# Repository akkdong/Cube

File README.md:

# M1
ESP32_WT32-SC01, Barometer, GPS, Audio, Battery bank

# M2
ESP32-S3-HMI-V3, Barometer, GPS, Audio, SD, Battery charge

# M3
M5Paper, EPS32-C3, Baromter, GPS, Audio

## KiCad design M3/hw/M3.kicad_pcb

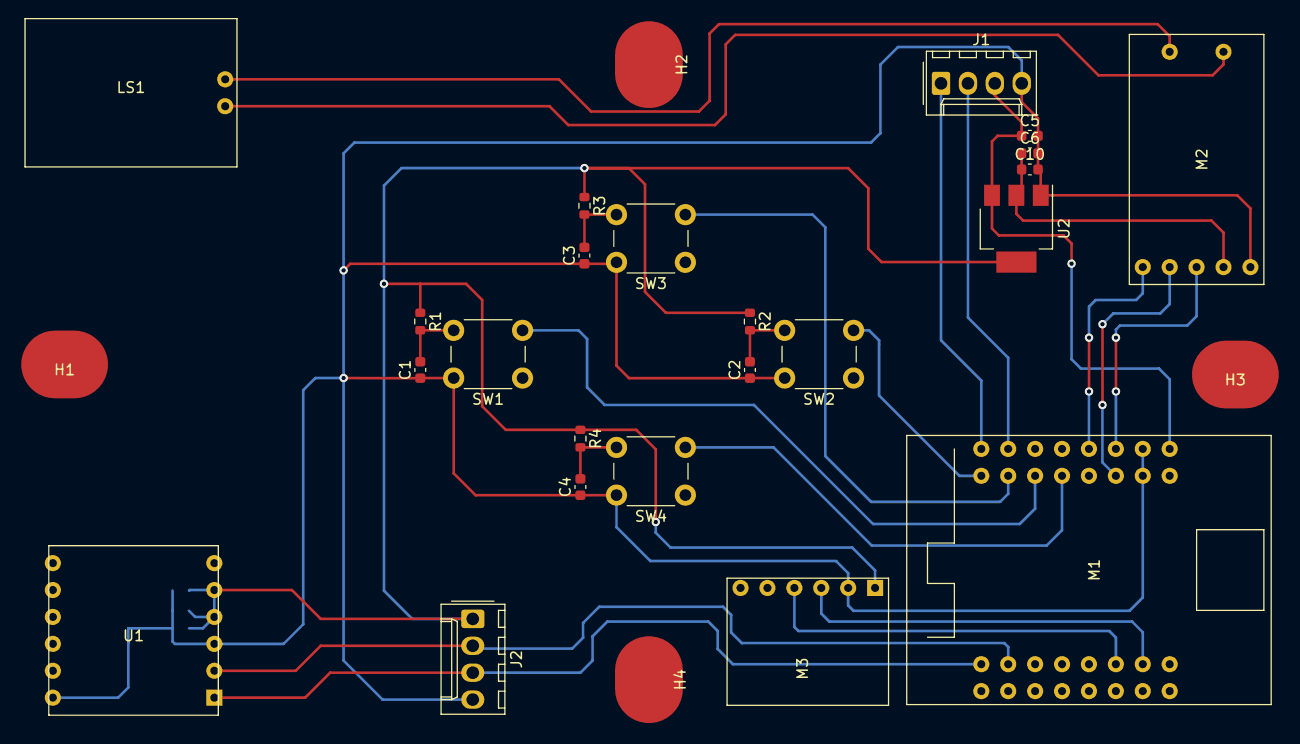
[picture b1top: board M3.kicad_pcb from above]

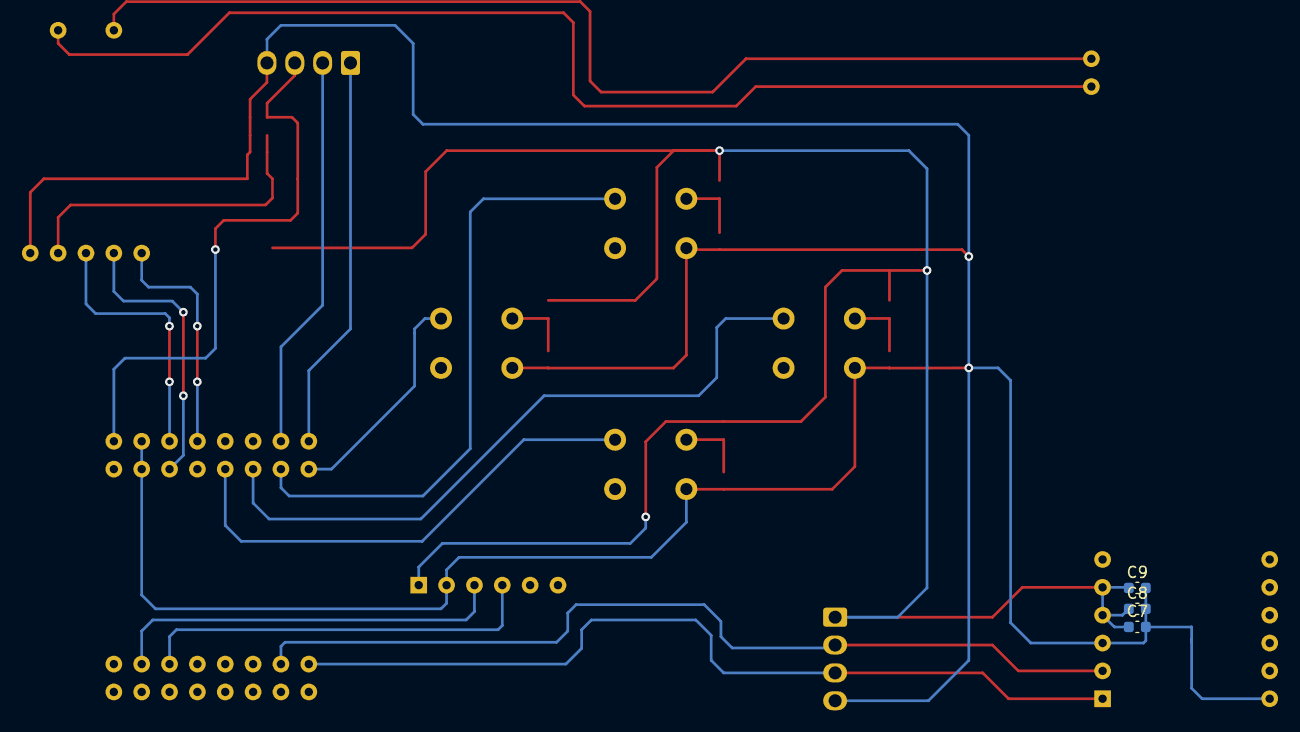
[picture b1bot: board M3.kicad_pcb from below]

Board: 2 copper layers, 30 parts (3 on the bottom side), 18 nets.

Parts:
C1, C2, C3, C4, C8, C9, C10: 0.1uF; C_0603_1608Metric
C5, C6, C7: 10uF; C_0603_1608Metric
H1, H2, H3, H4: MountingHole; M3_HOLE
J1, J2: Conn_01x04; Molex_KK-254_AE-6410-04A_1x04_P2.54mm_Vertical
LS1: Speaker; ROUND-SPEKAER
M1: EPS32S2-MINI; ESP32S2-MINI
M2: PAM8302A
M3: GY-BMP280
R1, R2, R3, R4: 10K; R_0603_1608Metric
SW1, SW2, SW3, SW4: SW_DIP_x01; SW_PUSH_6mm
U1: L80
U2: AP1117-33; SOT-223-3_TabPin2

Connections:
AUDIO+: M1.26, M2.1
AUDIO-: M1.27, M2.2
BARO_SCL: M1.14, M3.3
BARO_SDA: M1.12, M3.4
GND: C1.1, C2.1, C3.1, C4.1, C5.2, C6.2, C7.2, C8.2, C9.2, C10.2, J1.4, J2.4, M1.29, M1.30, M2.5, M3.2, SW1.1, SW2.1, SW3.1, SW4.1, U1.3, U1.12, U2.1
GPS_RX: J2.3, M1.2, U1.1
GPS_TX: J2.2, M1.4, U1.2
HOST_RX: J1.2, M1.20
HOST_TX: J1.1, M1.18
KEY_DOWN: C4.2, M1.23, R4.2, SW4.2
KEY_LEFT: C1.2, M1.21, R1.2, SW1.2
KEY_RIGHT: C2.2, M1.17, R2.2, SW2.2
KEY_UP: C3.2, M1.19, R3.2, SW3.2
MUTE: M1.28, M2.3
unnamed: LS1.1, M2.6
unnamed: LS1.2, M2.7
VBUS: C5.1, J1.3, M1.32, U2.3
VCC: C6.1, C7.1, C8.1, C9.1, C10.1, J2.1, M2.4, M3.1, R1.1, R2.1, R3.1, R4.1, U1.4, U1.5, U2.2

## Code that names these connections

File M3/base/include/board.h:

// board.h
//

#ifndef __BOARD_H__
#define __BOARD_H__

#define GPIO_I2C_SDA        (10)
#define GPIO_I2C_SCL        (13)

#define UART_HOST_RX        (39)    // device-side rx (host-side tx)
#define UART_HOST_TX        (37)    // device-side tx (host-side rx)

#define UART_GPS_RX         (2)     // device-side rx (gps-side tx)
#define UART_GPS_TX         (1)     // device-side tx (gps-side rx)

#define GPIO_KEY_UP         (38)
#define GPIO_KEY_DOWN       (34)
#define GPIO_KEY_LEFT       (36)
#define GPIO_KEY_RIGHT      (40)


#endif // __BOARD_H__

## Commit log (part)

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2022-09-07 documents
2022-09-07 images
2022-09-07 basic
2022-09-08 simulator
2022-09-08 logger
2022-09-12 page, box
2022-09-12 layout (TBD)
2022-09-15 filters
2022-09-15 esp32 port implement (not tested)
2022-09-15 bme280: disable humidity features & optimize
2022-09-15 refactoring
2022-09-15 fixed running-error
2022-09-16 tone play
2022-09-19 case-design
2022-09-19 update case-design
2022-09-19 readme
2022-09-20 update filter
2022-09-24 fixed build-error
2022-09-25 esp32 bt
2022-09-27 BLEVario reference
2022-09-27 acoustic test
2022-09-27 fixed ble-uart write error
2022-10-03 fixed build error
2022-10-03 update working-image
2022-10-03 implement annunciator (TBD)
2022-10-05 filter(kf4d) calibration
2022-10-16 timezone API & fixed filter error
2022-10-18 datasheet
2022-10-19 M2 H/W Test (TBD)
2022-10-19 H/W Test: touch
2022-10-20 H/W Test : lcd w/ lvgl (need test)
2022-10-20 H/W Test: audio, adc (TBD)
2022-10-23 M2 Test code
2022-10-23 M2 case
2022-10-23 HW Test : audio
2022-10-30 fixed layout
2022-10-30 calibrate kalman-filter
2022-10-31 update M2 variometer
2022-11-02 audio-test
2022-11-04 apply vario sound
2022-11-07 test keypad
2022-11-09 widget (working)
2022-11-13 new ui-framework
2022-11-13 startup window & variometer widget
2022-11-14 layout switching
2022-11-15 widgets
2022-11-15 setting-window skeleton
2022-11-16 setting skeleton
2022-11-16 use millis() instead get_tick()
2022-11-17 startup
2022-11-18 compass
2022-11-26 thermal-assistant
2022-11-28 use task
2022-11-30 task
2022-11-30 annunciator
2022-12-01 alert
2022-12-01 M2 new-ui
2022-12-03 new assets
2022-12-05 fixed simulator keypad-handler
2022-12-06 assets
2022-12-07 fixed igc-logging error
2022-12-07 32-icon
2022-12-07 missing files
2022-12-10 fixed nmea loosing
2022-12-10 move Accumulator
2022-12-14 test code
2022-12-21 M1 test...
2022-12-22 m2 refactoring (TBD)
2022-12-23 m2 refactoring(TBD)
2022-12-26 m2 refactoring
2022-12-27 pre-read
2022-12-28 tune
2023-01-07 refactory variometer bar
2023-03-08 rename
2023-03-09 m3 base & disp firmware
2023-03-12 add missing files
2023-03-12 beep
2023-03-13 m3 case
2023-04-03 fixed error of uart initialize
2023-04-13 cube nmea-sentence
2023-04-17 nmea parser (TBD)
2023-04-17 host command
2023-04-19 nmea parsing (TBD)
2023-04-20 show nmea data
2023-04-21 fixed nmea parsing
2023-08-02 M3 test code
2023-08-02 test
2023-08-03 M3 working (compile only)
2023-08-04 running test
2023-08-06 fixed SD error
2023-08-07 thermal assist (TBD)
2023-08-07 change icon-images
2023-08-08 changed source tree
2023-08-09 igc logger
2023-08-11 message box
2023-08-11 suppress log
2023-08-12 page
2023-08-12 changed baro-filter
2023-08-12 barometer
2023-08-12 m3 working
2023-08-16 fixed error of data loosing (TBD)
2023-08-18 pin task to core
2023-08-21 share SPI
2023-08-22 data
2023-08-22 remove unused sources
2023-08-22 pre-shutdown (?)
2023-08-24 fixed vario-logger error
2023-08-24 v-box types
2023-08-24 revert compile option
2023-09-01 top-menu
2023-09-16 change tone-table
2023-09-17 WiFiSetting (TBD)
2023-09-20 captive-portal (TBD)
2023-09-20 use full file-name
2023-09-21 web-service test server
2023-09-21 captive-portal:async (TBD)
2023-09-22 rollback to WebServer
2023-09-22 WebServer build configuration
2023-09-24 async-web-server again
2023-09-24 json type error, web pages, chunked file, bt end
2023-09-28 draw wifi setting page
2023-10-07 fixed label
2023-10-12 load xctask
2023-10-12 xctask sample
2023-10-14 task-simulator: load task & find optimized path
2023-10-14 recompute from pilot position
2023-10-14 xctrack is inherited from xcroute
2023-10-14 race-simulator image
2023-10-15 utils_geographiclib
2023-10-15 xctask test on target
2023-10-18 - changed geographiclib precision - some test code - and so on
2023-10-21 - save screen as file - change device-context
2023-10-21 volume & fixed some bug
2023-10-25 screen-shot
2023-10-27 up direction
2023-11-06 RaceSimulate -> RaceSimulator
2023-11-07 rename RaceSimulate to RaceSimulator
2023-11-20 another optimize method: test
